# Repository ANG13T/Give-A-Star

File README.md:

<div style="text-align:center" align="center">

</div>

<h3 style="text-align:center" align="center">A Star PCB Board based on the ESP32-S2 and D1 Mini to teach the basics of soldering</h3>

## Features
- Five Different LED Animations
- Change Animations by Clicking Button
- Teach the Basics of Soldering
- Great for Beginners

## Components
| Component | Purpose |
| --- | --- |
| **ESP32-S2** OR **ESP8266 D1 Mini** | Manage animations and code
| 128x64 SSH1106 OLED | Write a visual message to someone |
| Tactile Push Button | Change light animation |
| 6x LED | Display animations |
| 6x 100ohm Resistors | Manage voltage |

## Hardware Setup
**Top LED** 
| LED Pin | ESP32-S2 Pin | D1 Mini Pin |
| --- | --- | --- |
| VIN | 9 | D6 |
| GND | GND | GND |

**Right LED** 
| LED Pin | ESP32-S2 Pin | D1 Mini Pin |
| --- | --- | --- |
| VIN | 7 | D5 |
| GND | GND | GND |

**Bottom Right LED** 
| LED Pin | ESP32-S2 Pin | D1 Mini Pin |
| --- | --- | --- |
| VIN | 5 | D0 |
| GND | GND | GND |

**Left LED** 
| LED Pin | ESP32-S2 Pin | D1 Mini Pin |
| --- | --- | --- |
| VIN | 11 | D7 |
| GND | GND | GND |

**Bottom Left LED** 
| LED Pin | ESP32-S2 Pin | D1 Mini Pin |
| --- | --- | --- |
| VIN | 12 | D8 |
| GND | GND | GND |

**OLED SSH1106** 
| OLED Pin | ESP32-S2 Pin | D1 Mini Pin |
| --- | --- | --- |
| VCC | 3V3 | 3V3 |
| GND | GND | GND |
| SCK | 35 | D1 |
| SDA | 33 | D2 |

**Push Button** 
| Button Pin | ESP32-S2 Pin | D1 Mini Pin |
| --- | --- | --- |
| 1 | 3V3 | 3V3 |
| 2 | 16 | D4 |
| 2 | GND | GND |

## Breadboard

## Schematic

## PCB Design

## Photos
&nbsp;&nbsp;

## Set up
- Arduino IDE with the following URL added under Preferences -> Additional board manager URL's: http://arduino.esp8266.com/stable/package_esp8266com_index.json (D1 Mini) OR https://raw.githubusercontent.com/espressif/arduino-esp32/gh-pages/package_esp32_dev_index.json (ESP32-S2)

- ESP8266 boards added in Arduino IDE by going to Tools -> Boards -> Boards Manager, and installing ESP8266 by ESP8266 Community (D1 Mini)

- ESP32 boards added in Arduino IDE by going to Tools -> Boards -> Boards Manager, and installing ESP32 by Expressif Systems (ESP32-S2)

- Install Zip file from https://github.com/wonho-maker/Adafruit_SH1106 and unzip the file inside Arduino -> libraries

- Adafruit GFX library installed in Arduino IDE by going to Sketch -> Include Library -> Manage Libraries and installing "Adafruit GFX Library" by Adafruit

- Optional: Depending on which type of OLED screen you use, you might have to install this library [esp8266-oled-ssd1306](https://github.com/ThingPulse/esp8266-oled-ssd1306) or **SSD1306 by Adafruit:** Sketch -> Include Library -> Manage Libraries and installing "Adafruit GFX Library"

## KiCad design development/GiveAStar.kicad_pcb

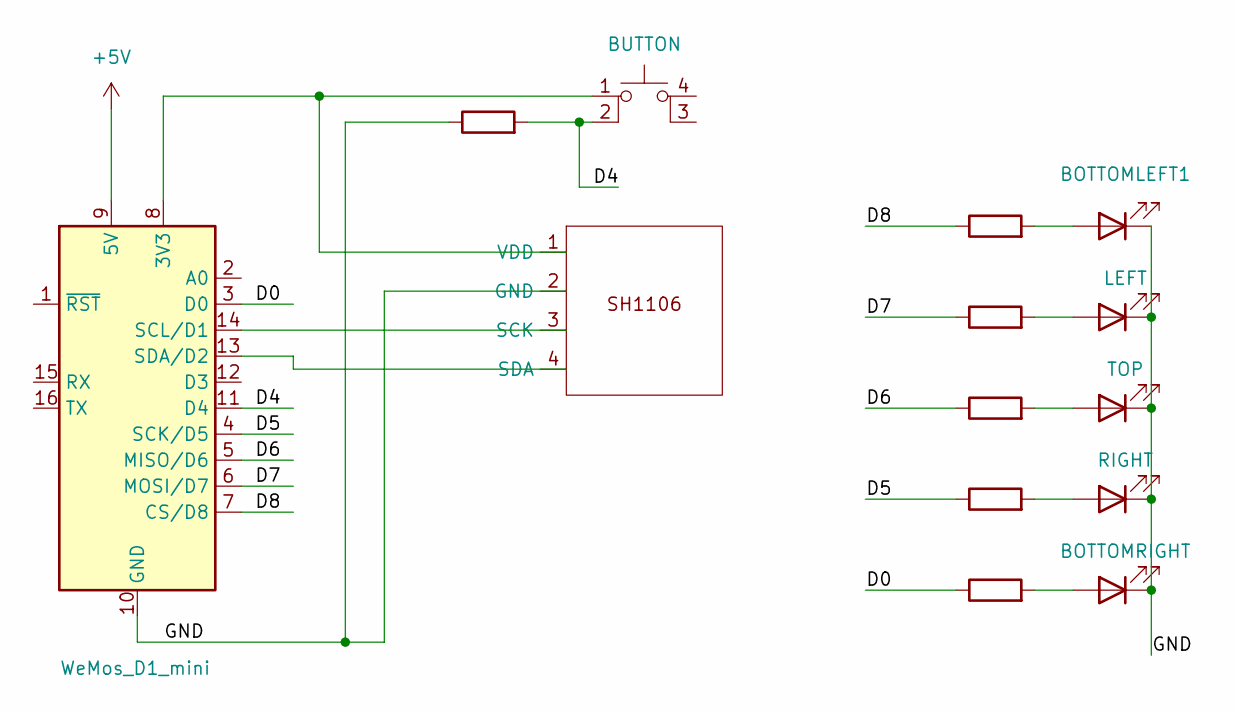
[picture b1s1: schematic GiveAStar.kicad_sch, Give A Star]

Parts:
.1, .2, .3, .4, .5, .6: R; R_Axial_DIN0204_L3.6mm_D1.6mm_P5.08mm_Horizontal
BOTTOMLEFT1: LEFT; LED_D3.0mm
D1: TOP; LED_D3.0mm
D2: RIGHT; LED_D3.0mm
D3: BOTTOMRIGHT; LED_D3.0mm
D4: LED; LED_D3.0mm
SW1: BUTTON; SW_PUSH_6mm
U1: WeMos_D1_mini; WEMOS_D1_mini_light
U2: SSH1106; Adafruit_SSH1106

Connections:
+5V: U1.9 (5V)
/D0: .6.1, U1.3 (D0)
/D4: .1.2, SW1.2, U1.11 (D4)
/D5: .5.1, U1.4 (SCK/D5)
/D6: .4.1, U1.5 (MISO/D6)
/D7: .3.1, U1.6 (MOSI/D7)
/D8: .2.1, U1.7 (CS/D8)
/GND: .1.1, BOTTOMLEFT1.1 (K), D1.1 (K), D2.1 (K), D3.1 (K), D4.1 (K), U1.10 (GND), U2.2 (GND)
unnamed: .2.2, BOTTOMLEFT1.2 (A)
unnamed: .3.2, D1.2 (A)
unnamed: .4.2, D2.2 (A)
unnamed: .5.2, D3.2 (A)
unnamed: .6.2, D4.2 (A)
unnamed: SW1.1, U1.8 (3V3), U2.1 (VDD)
unnamed: U1.13 (SDA/D2), U2.4 (SDA)
unnamed: U1.14 (SCL/D1), U2.3 (SCK)

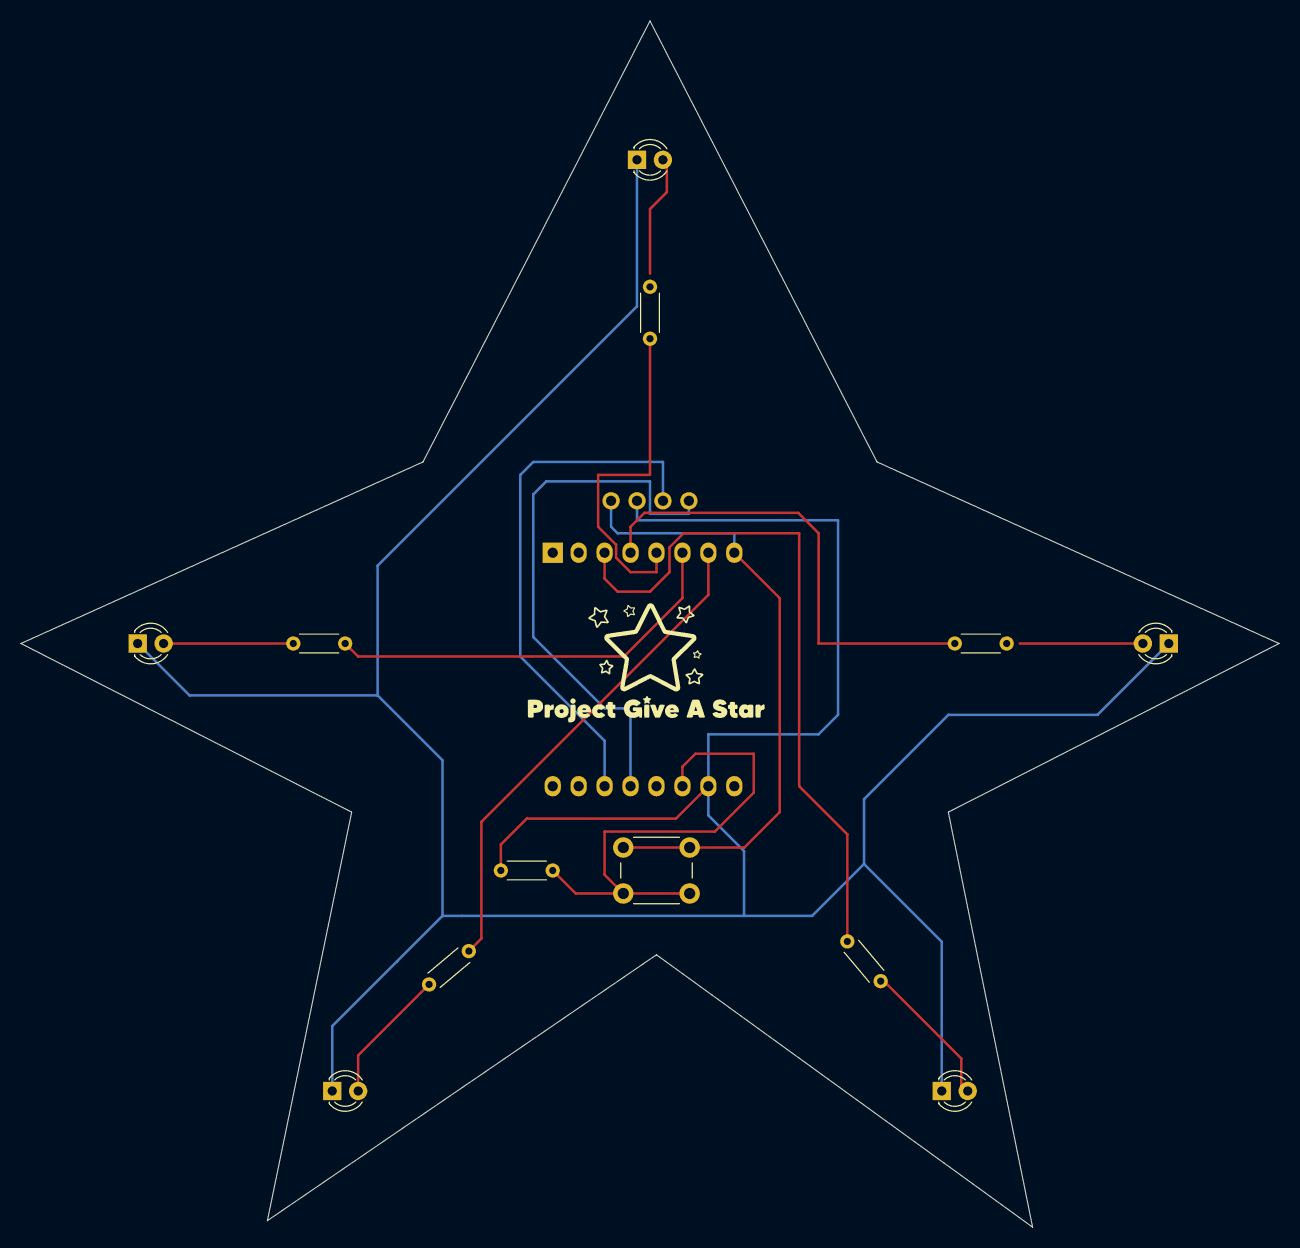
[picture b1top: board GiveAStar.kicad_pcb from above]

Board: 2 copper layers, 123.2 x 118.1 mm, 14 parts (1 on the bottom side), 15 nets.

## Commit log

2022-11-30 init commit
2022-11-30 init OLED configuration
2022-12-07 feat: init button input
2022-12-07 init graphics
2022-12-07 init graphics file
2022-12-07 fix graphics display
2022-12-08 feat: update logo
2022-12-08 feat: init button func
2022-12-08 feat: init basic led logic
2022-12-08 feat: init all led sequences
2022-12-08 feat: init concurrency
2022-12-10 fix: in order animation
2022-12-10 feat: MVP of star animations
2022-12-10 feat: star animations complete
2022-12-10 Make Text Slideshow
2022-12-14 feat: update star script
2022-12-14 feat: upload assets
2022-12-14 feat: upload main
2022-12-14 feat: update assets
2022-12-14 edit assets
2022-12-15 Init LED Pinouts
2022-12-15 Init OLED Pin Outs
2022-12-15 Init Push Button Pin Outs
2022-12-15 feat: init development
2023-01-08 feat: reformat dirs
2023-01-26 feat: remove animations
2023-01-26 feat: init new star assets
2023-01-26 feat: init multitasking
2023-01-26 feat: change xbm names
2023-01-26 feat: update graphics
2023-01-26 feat: update showStarImage
2023-01-26 feat: commented code
2023-01-26 Upload images
